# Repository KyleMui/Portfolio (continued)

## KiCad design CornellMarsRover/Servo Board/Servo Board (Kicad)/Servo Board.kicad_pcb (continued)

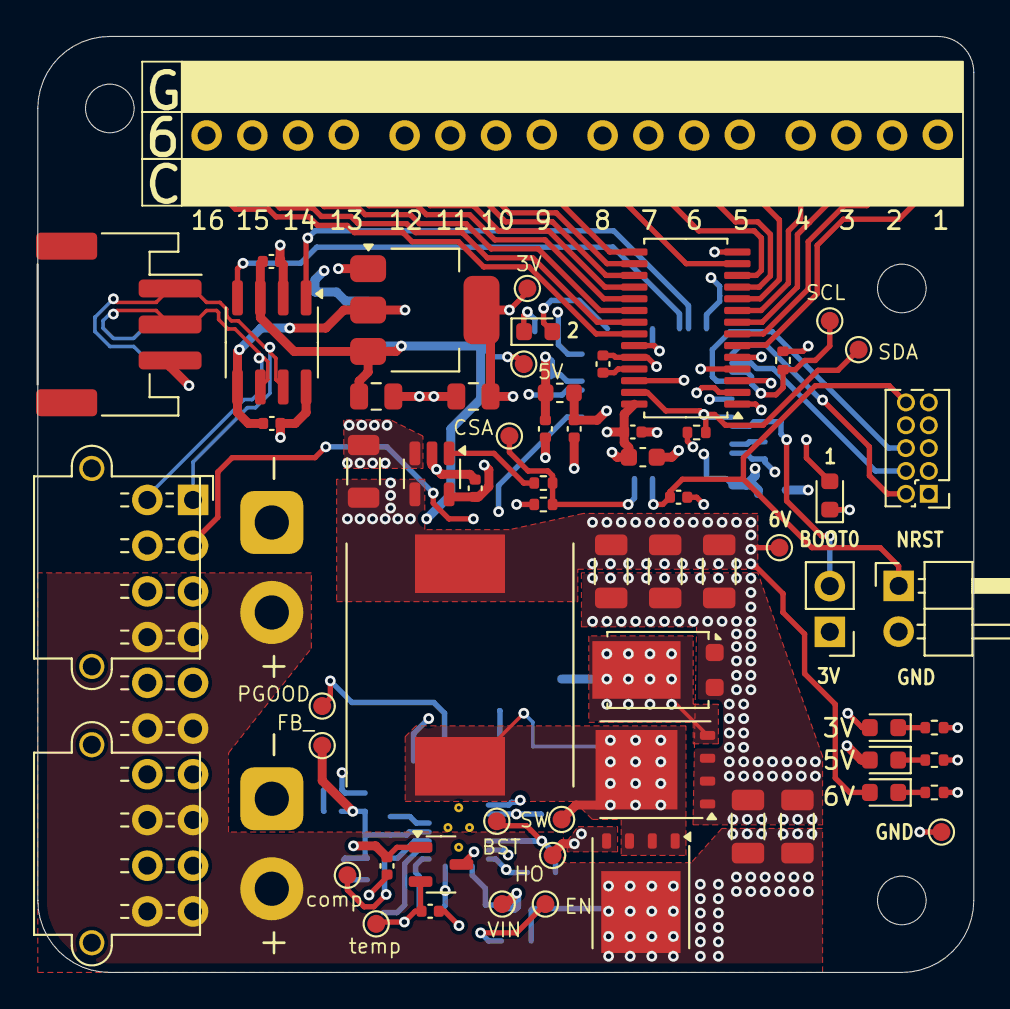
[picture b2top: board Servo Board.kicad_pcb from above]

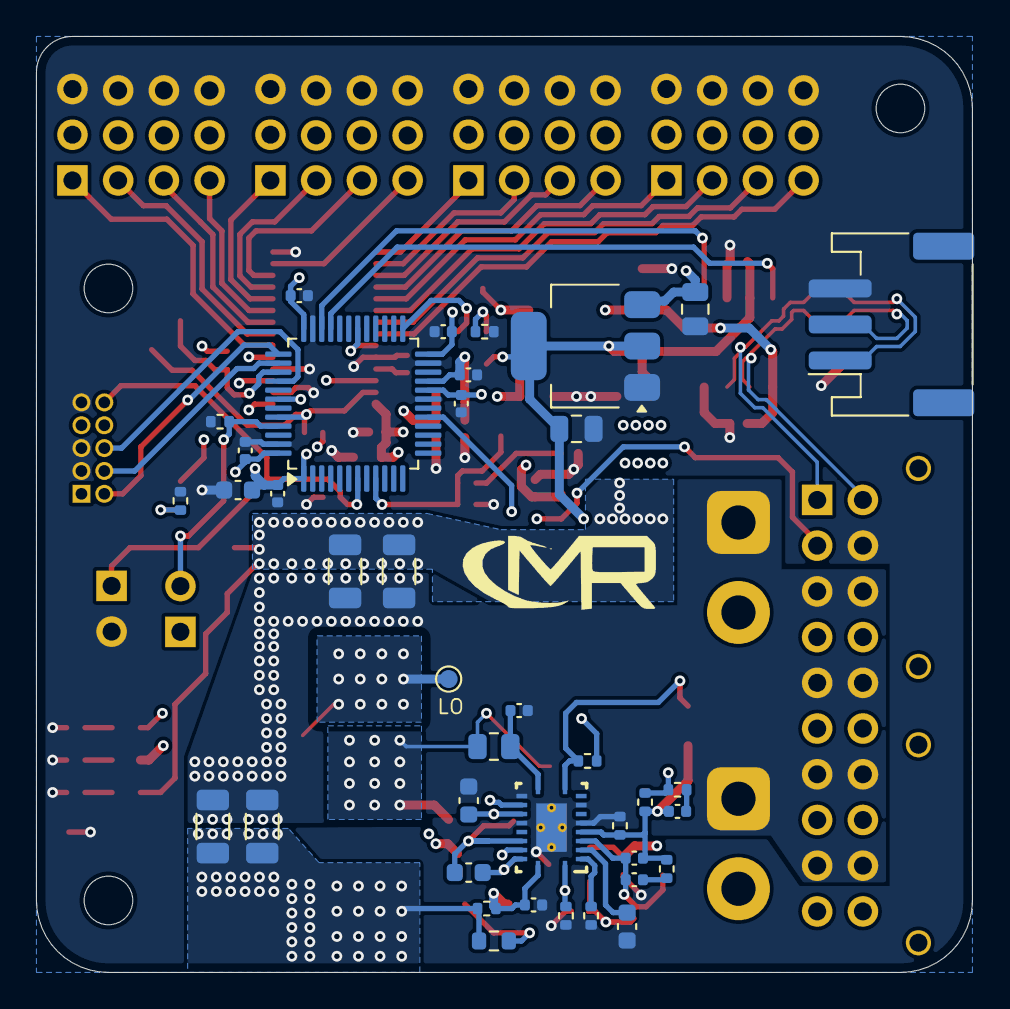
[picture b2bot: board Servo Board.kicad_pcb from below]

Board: 4 copper layers, 52.0 x 52.0 mm, 110 parts (39 on the bottom side), 60 nets.

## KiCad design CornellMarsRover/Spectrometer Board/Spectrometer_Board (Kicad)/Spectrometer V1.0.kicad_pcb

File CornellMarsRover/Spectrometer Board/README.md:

# Spectrometer Board

## Overview
The Spectrometer Board is a custom-made circuit designed for the Cornell Mars Rover Project to help analyze soil and rock samples. It works by shining light on the samples and then measuring the light that passes through using a photodiode.

The board has LEDs to light up the samples and a photodiode to detect how much light is reflected or transmitted. An op-amp on the board boosts the current from the photodiode and converts it into a measurable voltage. This voltage gives the science team useful info about what the samples are made of and their optical properties.

---

## Key Features
- Photodiode sensor for precise analog light intensity measurement  
- Op-amp signal conditioning stage for current-to-voltage conversion and amplification  
- LED driver circuit for controlled and consistent sample illumination  
- Amplified voltage output proportional to detected light intensity  
- Uses a STM32G431CBT6 microcontroller  
- CAN FD communication interface for integration with the rover’s main control network  
- 28 V power input with onboard regulation for 5 V and 3.3 V rails  

---

## Function
1. Light Emission:
   The onboard LEDs emit light through a soil or rock sample that's in its path.

2. Detection:
   The photodiode reads the intensity of the light, inducing a current that matches how much light there is.

3. Filtering and Amplification:
   The onboard op-amp converts and amplifies the photodiode’s current into a stable voltage output, filtered for noise reduction and precision.

4. Data Transmission:
   The STM32G431CBT6 microcontroller takes in the conditioned voltage signal and sends the measurement data to the rover’s NVIDIA Jetson Orin Nano using CAN FD. The science team then uses this info for real-time material analysis.
---

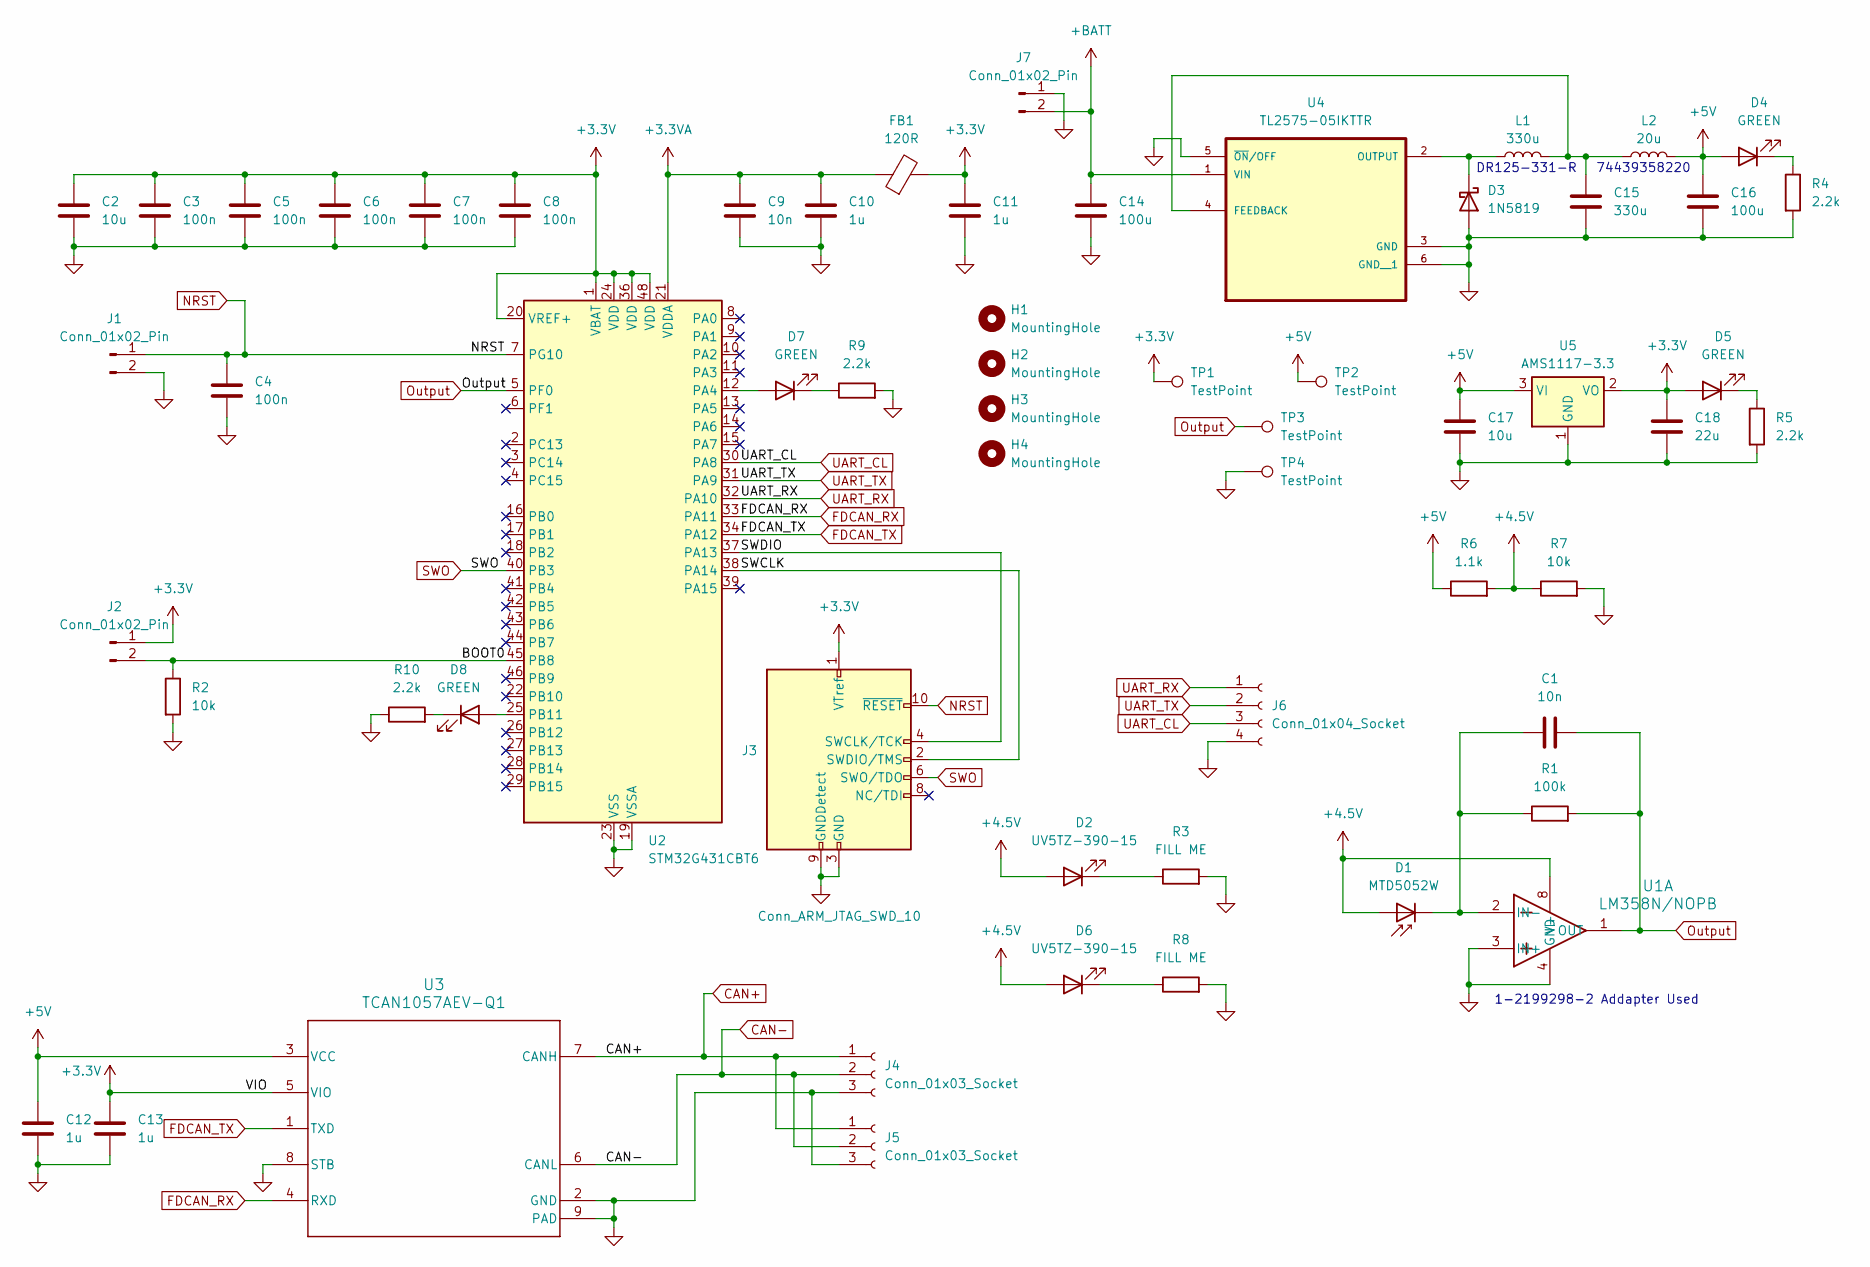
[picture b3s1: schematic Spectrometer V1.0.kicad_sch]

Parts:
C1: 10n; C_Rect_L4.0mm_W2.5mm_P2.50mm
C2: 10u; C_0603_1608Metric
C3, C4, C5, C6, C7, C8: 100n; C_0402_1005Metric
C9: 10n; C_0402_1005Metric
C10, C11, C12, C13: 1u; C_0402_1005Metric
C14: 100u; C_Radial_D8.0mm_H11.5mm_P3.50mm
C15: 330u; C_1210_3225Metric
C16: 100u; C_0805_2012Metric
C17: 10u; C_0805_2012Metric
C18: 22u; C_0805_2012Metric
D1: MTD5052W; LED_D5.0mm
D2, D6: UV5TZ-390-15; LED_D5.0mm
D3: 1N5819; D_DO-41_SOD81_P7.62mm_Horizontal
D4, D5, D7, D8: GREEN; LED_0603_1608Metric
FB1: 120R; L_0603_1608Metric
H1, H2, H3, H4: MountingHole; MountingHole_3.2mm_M3
J1, J2: Conn_01x02_Pin; PinHeader_1x02_P2.54mm_Vertical
J3: Conn_ARM_JTAG_SWD_10; PinHeader_2x05_P1.27mm_Vertical
J4, J5: Conn_01x03_Socket; JST_PH_S3B-PH-SM4-TB_1x03-1MP_P2.00mm_Horizontal
J6: Conn_01x04_Socket; JST_ZE_S04B-ZESK-2D_1x04_P1.50mm_Horizontal
J7: Conn_01x02_Pin; AMASS_XT30PW-M_1x02_P2.50mm_Horizontal
L1: 330u; DR125
L2: 20u; WE-XHMI_8080
R1: 100k; R_Axial_DIN0204_L3.6mm_D1.6mm_P7.62mm_Horizontal
R2: 10k; R_0402_1005Metric
R3, R8: FILL ME; R_Axial_DIN0204_L3.6mm_D1.6mm_P7.62mm_Horizontal
R4, R5, R9, R10: 2.2k; R_0402_1005Metric
R6: 1.1k; R_Axial_DIN0204_L3.6mm_D1.6mm_P7.62mm_Horizontal
R7: 10k; R_Axial_DIN0204_L3.6mm_D1.6mm_P7.62mm_Horizontal
TP1, TP2, TP3, TP4: TestPoint; TestPoint_Pad_D1.0mm
U1: LM358N/NOPB; CONN8_1-2199298-2_TEC
U2: STM32G431CBT6; LQFP-48_7x7mm_P0.5mm
U3: TCAN1057AEV-Q1; SOIC-8_3.9x4.9mm_P1.27mm; MPN TCAN1057AEVDRQ1
U4: TL2575-05IKTTR; TO-263-5_TabPin6
U5: AMS1117-3.3; SOT-223-3_TabPin2

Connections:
+3.3V: C2.1, C3.1, C5.1, C6.1, C7.1, C8.1, C11.1, C13.1, C18.1, D5.2 (A), FB1.2, J2.1, J3.1 (VTref), TP1.1, U2.1 (VBAT), U2.20 (VREF+), U2.24 (VDD), U2.36 (VDD), U2.48 (VDD), U3.5 (VIO), U5.2 (VO)
+3.3VA: C9.1, C10.1, FB1.1, U2.21 (VDDA)
+4.5V: D1.2 (A), D2.2 (A), D6.2 (A), R6.2, R7.1, U1.8 (V+)
+5V: C12.1, C16.1, C17.1, D4.2 (A), L2.2, R6.1, TP2.1, U3.3 (VCC), U5.3 (VI)
+BATT: C14.1, J7.2, U4.1 (VIN)
/BOOT0: J2.2, R2.1, U2.45 (PB8)
/SWCLK: J3.2 (SWDIO/TMS), U2.38 (PA14)
/SWDIO: J3.4 (SWCLK/TCK), U2.37 (PA13)
CAN+: J4.1, J5.1, U3.7 (CANH)
CAN-: J4.2, J5.2, U3.6 (CANL)
FDCAN_RX: U2.33 (PA11), U3.4 (RXD)
FDCAN_TX: U2.34 (PA12), U3.1 (TXD)
GND: C2.2, C3.2, C4.2, C5.2, C6.2, C7.2, C8.2, C9.2, C10.2, C11.2, C12.2, C13.2, C14.2, C15.2, C16.2, C17.2, C18.2, D3.2 (A), J1.2, J3.3 (GND), J3.5 (GND), J3.9 (GNDDetect), J4.3, J5.3, J6.4, J7.1, R2.2, R3.2, R4.2, R5.2, R7.2, R8.2, R9.2, R10.1, TP4.1, U1.3 (IN+), U1.4 (GND), U2.19 (VSSA), U2.23 (VSS), U2.35 (VSS), U2.47 (VSS), U3.2 (GND), U3.8 (STB), U3.9 (PAD), U4.3 (GND), U4.5 (~ON/OFF), U4.6 (GND__1), U5.1 (GND)
NRST: C4.1, J1.1, J3.10 (~RESET), U2.7 (PG10)
unnamed: C1.1, D1.1 (K), R1.1, U1.2 (IN-)
unnamed: D2.1 (K), R3.1
unnamed: D3.1 (K), L1.1, U4.2 (OUTPUT)
unnamed: D4.1 (K), R4.1
unnamed: D5.1 (K), R5.1
unnamed: D6.1 (K), R8.1
unnamed: D7.2 (A), U2.12 (PA4)
unnamed: D7.1 (K), R9.1
unnamed: D8.2 (A), U2.25 (PB11)
unnamed: D8.1 (K), R10.2
unnamed: C15.1, L1.2, L2.1, U4.4 (FEEDBACK)
Output: C1.2, R1.2, TP3.1, U1.1 (OUT), U2.5 (PF0)
SWO: J3.6 (SWO/TDO), U2.40 (PB3)
UART_CL: J6.3, U2.30 (PA8)
UART_RX: J6.1, U2.32 (PA10)
UART_TX: J6.2, U2.31 (PA9)

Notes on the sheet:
DR125-331-R
74439358220
1-2199298-2 Addapter Used

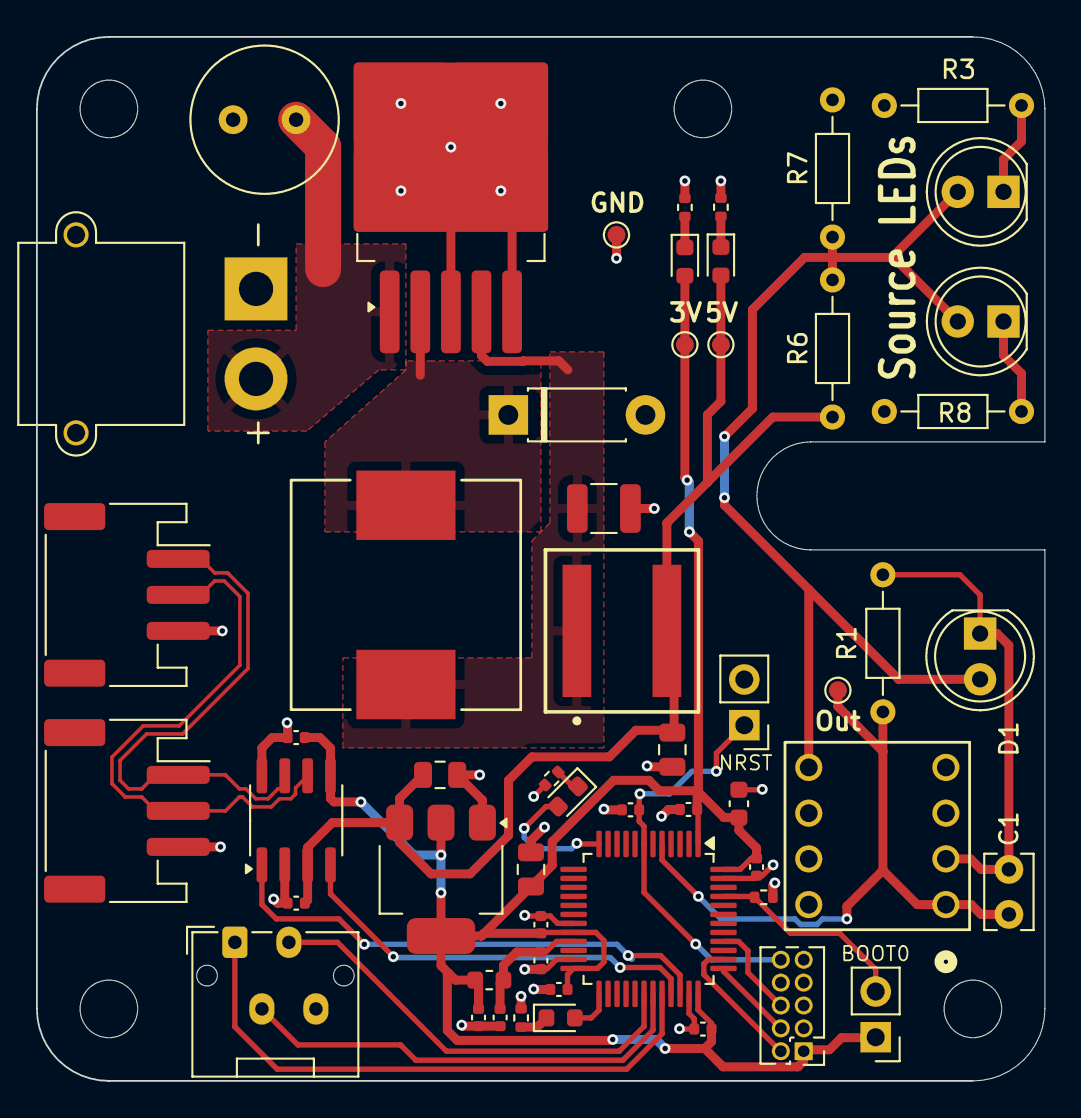
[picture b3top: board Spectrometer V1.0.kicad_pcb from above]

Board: 2 copper layers, 56.0 x 58.0 mm, 59 parts (0 on the bottom side), 30 nets.

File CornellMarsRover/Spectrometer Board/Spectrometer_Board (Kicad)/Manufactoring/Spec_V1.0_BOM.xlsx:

|  |  | xxxx xxxx xxxxx xxPCS BOM (Sample Bill of Materials)
Item # | *Designator | *Qty | Manufacturer | *Mfg Part # | Description / Value | *Package/Footprint | Type | Your Instructions / Notes
1 | C1 | 1 | KEMET | C315C103K5R5TA | 10nF | Radial | THT
2 | C2 | 1 | Samsung Electro-Mechanics | CL10A106KQ8NNNC | 10uF | 0603 | SMD
3 | C3-C8 | 6 | Samsung Electro-Mechanics | CL05B104KP5NNNC | 100n | 0402 | SMD
4 | C9 | 1 | Samsung Electro-Mechanics | CL05B103KB5NNNC | 10nF | 0402 | SMD
5 | C10-C13 | 4 | Samsung Electro-Mechanics | CL05A105KP5NNNC | 1uF | 0402 | SMD
6 | C14 | 1 | Rubycon | 50YXJ100MT78X11.5 | 100uF | Radial | THT
7 | C15 | 1 | Taiyo Yuden | JMK325ABJ337MM-PE | 330uF | 1210 | SMD
8 | C16 | 1 | Samsung Electro-Mechanics | CL21A107MQYNNWE | 100uF | 0805 | SMD
9 | C17 | 1 | Samsung Electro-Mechanics | CL21A106KOQNNNE | 10uF | 0805 | SMD
10 | C18 | 1 | Samsung Electro-Mechanics | CL21A226MQQNNNE | 22uF | 0805 | SMD
11 | D1 | 1 | Marktech Optoelectronics | MTD5052W | 525nm photodiode | non-standard | THT
12 | D2, D6 | 2 | Bivar Inc. | UV5TZ-390-15 | 390nm LED | Radial | THT
13 | D3 | 1 | STMicroelectronics | 1N5819 | Schottky Diode | DO-41 | THT
14 | D4, D5, D7, D8 | 4 | Würth Elektronik | 150060GS75000 | Green LED | 0603 | SMD
15 | FB1 | 1 | Murata Electronics | BLM18KG121TN1D | 120 Ohms @ 100MHz Ferrite Bead | 0603 | SMD
16 | J1, J2 | 2 | Würth Elektronik | 61300211121 | 1x2 2.54mm Vertical Pin Header | 1x2_P2.54mm | THT
17 | J3 | 1 | GCT | BD120-10-A-0305-0229-L-B | 2x5 1.27mm Vertical Pin Header | 2x5_P1.27mm | THT
18 | J4, J5 | 2 | JST Sales America Inc. | S3B-PH-SM4-TB | JST 3 Pin Connector | JST_PH_S3B-PH-SM4-TB_1x03-1MP_P2.00mm_Horizontal | SMD
19 | J6 | 1 | JST Sales America Inc. | S04B-ZESK-2D | CONN HEADER R/A 4POS 1.5MM | non-standard | THT
20 | J7 | 1 | AMASS | XT30PW-M | XT30 Connector | AMASS_XT30PW-M_1x02_P2.50mm_Horizontal | THT
21 | L1 | 1 | Eaton - Electronics Division | DR125-331-R | 330u | non-standard | SMD
22 | L2 | 1 | Würth Elektronik | 74439358220 | 20u | non-standard | SMD
23 | R1 | 1 | TE Connectivity Passive Product | ROX3SJ100K | 100k | Axial | THT
24 | R2 | 1 | Samsung Electro-Mechanics | RC1005F103CS | 10k | 0402 | SMD
25 | R3, R8 | DNP | DNP | DNP | DNP | DNP | DNP | DO NOT PLACE
26 | R3, R4, R9, R10 | 4 | YAGEO | RC0402FR-072K2L | 2.2k | 0402 | SMD
27 | R6 | 1 | Stackpole Electronics Inc | CF14JT1K10 | 1.1k | Axial | THT
28 | R7 | 1 | Stackpole Electronics Inc | RNF14FTD10K0 | 10k | Axial | THT
29 | U1 | 1 | TE Connectivity AMP Connectors | 1-2199298-2 | CONN IC DIP SOCKET 8POS TIN | non-standard | THT
30 | U2 | 1 | STMicroelectronics | STM32G431CBT6 | Microcontroller | LQFP-48_7x7mm_P0.5mm | SMD
31 | U3 | 1 | Texas Instruments | TCAN1057AEVDRQ1 | FDCAN Transiever | SOIC-8_3.9x4.9mm_P1.27mm | SMD
32 | U4 | 1 | Texas Instruments | TL2575-05IKTTR | 5V Buck Regulator | TO-263 | SMD
33 | U5 | 1 | UMW | AMS1117-3.3 | 3.3V Regulator | SOT-223-3_TabPin3 | SMD

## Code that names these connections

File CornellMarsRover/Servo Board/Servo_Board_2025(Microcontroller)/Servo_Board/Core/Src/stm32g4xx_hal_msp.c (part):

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    __HAL_RCC_GPIOA_CLK_ENABLE();
    __HAL_RCC_GPIOB_CLK_ENABLE();
    /**ADC1 GPIO Configuration
    PA1     ------> ADC1_IN2
    PB1     ------> ADC1_IN12
    */
    GPIO_InitStruct.Pin = CSA_Pin;
    GPIO_InitStruct.Mode = GPIO_MODE_ANALOG;
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    __HAL_RCC_ADC12_CLK_DISABLE();

    /**ADC1 GPIO Configuration
    PA1     ------> ADC1_IN2
    PB1     ------> ADC1_IN12
    */
    HAL_GPIO_DeInit(CSA_GPIO_Port, CSA_Pin);

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
    __HAL_RCC_GPIOA_CLK_ENABLE();
    /**FDCAN1 GPIO Configuration
    PA11     ------> FDCAN1_RX
    PA12     ------> FDCAN1_TX
    */
    GPIO_InitStruct.Pin = GPIO_PIN_11|GPIO_PIN_12;
    GPIO_InitStruct.Mode = GPIO_MODE_AF_PP;
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    __HAL_RCC_FDCAN_CLK_DISABLE();

    /**FDCAN1 GPIO Configuration
    PA11     ------> FDCAN1_RX
    PA12     ------> FDCAN1_TX
    */
    HAL_GPIO_DeInit(GPIOA, GPIO_PIN_11|GPIO_PIN_12);

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    __HAL_RCC_GPIOA_CLK_ENABLE();
    __HAL_RCC_GPIOB_CLK_ENABLE();
    /**I2C1 GPIO Configuration
    PA15     ------> I2C1_SCL
    PB7     ------> I2C1_SDA
    */
    GPIO_InitStruct.Pin = PWM_SCL_Pin;
    GPIO_InitStruct.Mode = GPIO_MODE_AF_OD;
    GPIO_InitStruct.Pull = GPIO_NOPULL;
    GPIO_InitStruct.Speed = GPIO_SPEED_FREQ_LOW;
    GPIO_InitStruct.Alternate = GPIO_AF4_I2C1;
    HAL_GPIO_Init(PWM_SCL_GPIO_Port, &GPIO_InitStruct);

    GPIO_InitStruct.Pin = PWM_SDA_Pin;
    GPIO_InitStruct.Mode = GPIO_MODE_AF_OD;
    GPIO_InitStruct.Pull = GPIO_NOPULL;
    GPIO_InitStruct.Speed = GPIO_SPEED_FREQ_LOW;
    GPIO_InitStruct.Alternate = GPIO_AF4_I2C1;
    HAL_GPIO_Init(PWM_SDA_GPIO_Port, &GPIO_InitStruct);

    /* Peripheral clock enable */
    __HAL_RCC_I2C1_CLK_ENABLE();
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    __HAL_RCC_I2C1_CLK_DISABLE();

    /**I2C1 GPIO Configuration
    PA15     ------> I2C1_SCL
    PB7     ------> I2C1_SDA
    */
    HAL_GPIO_DeInit(PWM_SCL_GPIO_Port, PWM_SCL_Pin);

    HAL_GPIO_DeInit(PWM_SDA_GPIO_Port, PWM_SDA_Pin);

<<<<<<< HEAD
    /* USER CODE BEGIN I2C1_MspDeInit 1 */
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
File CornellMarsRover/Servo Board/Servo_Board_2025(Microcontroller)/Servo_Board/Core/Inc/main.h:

/* USER CODE BEGIN Header */
/**
  ******************************************************************************
  * @file           : main.h
  * @brief          : Header for main.c file.
  *                   This file contains the common defines of the application.
  ******************************************************************************
  * @attention
  *
  * Copyright (c) 2024 STMicroelectronics.
  * All rights reserved.
  *
  * This software is licensed under terms that can be found in the LICENSE file
  * in the root directory of this software component.
  * If no LICENSE file comes with this software, it is provided AS-IS.
  *
  ******************************************************************************
  */
/* USER CODE END Header */

/* Define to prevent recursive inclusion -------------------------------------*/
#ifndef __MAIN_H
#define __MAIN_H

#ifdef __cplusplus
extern "C" {
#endif

/* Includes ------------------------------------------------------------------*/
#include "stm32g4xx_hal.h"

/* Private includes ----------------------------------------------------------*/
/* USER CODE BEGIN Includes */

/* USER CODE END Includes */

/* Exported types ------------------------------------------------------------*/
/* USER CODE BEGIN ET */

/* USER CODE END ET */

/* Exported constants --------------------------------------------------------*/
/* USER CODE BEGIN EC */

/* USER CODE END EC */

/* Exported macro ------------------------------------------------------------*/
/* USER CODE BEGIN EM */

/* USER CODE END EM */

/* Exported functions prototypes ---------------------------------------------*/
void Error_Handler(void);

/* USER CODE BEGIN EFP */

/* USER CODE END EFP */

/* Private defines -----------------------------------------------------------*/
#define NRST_Pin GPIO_PIN_10
#define NRST_GPIO_Port GPIOG
#define CSA_Pin GPIO_PIN_1
#define CSA_GPIO_Port GPIOA
#define Debug_LED1_Pin GPIO_PIN_3
#define Debug_LED1_GPIO_Port GPIOA
#define TEMP_Pin GPIO_PIN_1
#define TEMP_GPIO_Port GPIOB
#define OE_Pin GPIO_PIN_8
#define OE_GPIO_Port GPIOA
#define SWDIO_Pin GPIO_PIN_13
#define SWDIO_GPIO_Port GPIOA
#define SWCLK_Pin GPIO_PIN_14
#define SWCLK_GPIO_Port GPIOA
#define PWM_SCL_Pin GPIO_PIN_15
#define PWM_SCL_GPIO_Port GPIOA
#define SWO_Pin GPIO_PIN_3
#define SWO_GPIO_Port GPIOB
#define PWM_SDA_Pin GPIO_PIN_7
#define PWM_SDA_GPIO_Port GPIOB
#define BOOT0_Pin GPIO_PIN_8
#define BOOT0_GPIO_Port GPIOB

/* USER CODE BEGIN Private defines */

/* USER CODE END Private defines */

#ifdef __cplusplus
}
#endif

#endif /* __MAIN_H */

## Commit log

2025-11-08 add files
2025-11-08 add readme
2025-11-08 add all
2025-11-08 readme to just it
2026-01-05 add fan board
